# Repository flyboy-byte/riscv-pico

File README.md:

<h1 align="center">riscv-pico</h1>

<p align="center">
  <strong>A Raspberry Pi Pico running real Linux, with its own keyboard and screen.</strong><br>
  The RP2040 emulates a RISC-V CPU, SPI PSRAM becomes system memory,<br>
  and the Linux guest drives real GPIO pins.
</p>

<p align="center">
  <a href="https://flyboy-byte.github.io/riscv-pico/"><b>Website</b></a> •
  <a href="#try-it-in-60-seconds-no-hardware">Try it</a> •
  <a href="#how-it-actually-works">How it works</a> •
  <a href="#build-one-yourself">Build one</a> •
  <a href="#programming-on-the-pico">Programming</a> •
  <a href="#downloads">Downloads</a> •
  <a href="PLAN.md">PLAN.md</a>
</p>

<p align="center">
  <b>The story, photos, full pin map and wiring diagrams:
  <a href="https://flyboy-byte.github.io/riscv-pico/">flyboy-byte.github.io/riscv-pico</a></b>
</p>

---

> [!NOTE]
> **This is a build log, not an upstream improvement.** It's my own vibe-coded "Linux on a Pico"
> project — the real projects below did the hard work; this repo forks, ports, and glues them
> together and writes down what happened. Posted in case it's useful to someone chasing the same
> idea. The code, docs, and this README were written by
> [Claude Code](https://claude.com/claude-code); I directed it, tested on real hardware, and made
> the calls.

### Built on

| Project | What it gave this repo |
| --- | --- |
| **[tvlad1234/pico-rv32ima](https://github.com/tvlad1234/pico-rv32ima)** + **[tiny-rv32ima](https://github.com/tvlad1234/tiny-rv32ima)** | **The fork point.** Actively maintained, the emulator core, and the VGA and PS/2 console code. |
| [ElectroBoy404NotFound/pico-linux](https://github.com/ElectroBoy404NotFound/pico-linux) | The multi-chip PSRAM port and LCD console approach. |
| [cnlohr/mini-rv32ima](https://github.com/cnlohr/mini-rv32ima) | The original RV32IMA-in-C emulator all of the above descends from. |
| [xhackerustc/uc-rv32ima](https://github.com/xhackerustc/uc-rv32ima) | The cache implementation this actually runs. |
| [rswier/c4](https://github.com/rswier/c4) via [tvlad1234/c4](https://github.com/tvlad1234/c4) | The C compiler that runs on the machine itself. |

**Go star their repos, not this one.**

---

## The short version

A Pico has no MMU and about 264 KB of RAM. It was never meant to run an operating system. So:
core 1 of the RP2040 runs a full RV32IMA interpreter, two SPI PSRAM chips stand in for system
memory, and an SD card holds the kernel and root filesystem. Linux boots on top of that — and
custom kernel drivers let the guest reach back out through the emulator to drive **real hardware**.

Add a PS/2 keyboard, a VGA monitor and a breadboard power supply, and it runs with no computer
attached. You can write a program in nano on the Pico, run it, and have it blink an LED.

<p align="center"><sub>The OLED is reporting on the machine it's plugged into: 16 MB across 2 chips, live MIPS, uptime, 400 MHz clock.</sub></p>

And running on its own: PS/2 keyboard in, VGA monitor out, no PC anywhere.

| | |
|---|---|
|  |  |
| `sysinfo`: Linux 6.6 on an emulated RV32, 14 MB of RAM | GNU nano editing `hello.c`, full screen |
|  |  |
| Tiny BASIC, then c4 compiling and running that `hello.c` | Minesweeper, in Lua |

---

## Status

What's actually verified, versus what merely compiles. No wishful thinking in this table.

| | Feature | Notes |
|---|---|---|
| ✅ | **Linux boots on a real Pico** | RP2040, 16 MB PSRAM, 60 MB rootfs off SD. Shell in well under a minute. |
| ✅ | **Runs standalone** | PS/2 keyboard in, VGA out, its own power supply. Files edited and saved with no PC attached. |
| ✅ | **GPIO from Linux → real pins** | Both `/dev/gpiochipN` (chardev + `libgpiod`) *and* `/sys/class/gpio`. Verified lighting an actual LED. |
| ✅ | **Runs real software** | Tiny BASIC, Lua 5.4.7, GNU nano 7.2 (full-screen), `sysinfo`, and minesweeper. |
| ✅ | **nano on the VGA screen** | Firmware v6 rewrote the VGA terminal as a VT102, so nano draws correctly at 53×30. Verified on hardware. On v5, nano over VGA is unusable. |
| ✅ | **Custom kernel drivers** | Block device, GPIO, second console channel — real Linux drivers, not shims. |
| ✅ | **Desktop harness** | Boots the same kernel on your PC in a few seconds. No hardware needed. |
| ✅ | **SSD1306 OLED panel** | A live stats visualizer. Not essential, just fun. |
| ✅ | **Programming on the Pico** | Lua with sleep and raw key input, GPIO from Lua and the shell, the c4 C compiler, BASIC's `BYE`, and minesweeper. All verified on hardware. |
| ✅ | **Slimmer kernel** | Networking removed, about 1 MB of RAM back. Boots on hardware. |
| 🚧 | **`pico2` / `pico2_w` (RP2350)** | Builds clean for all four board targets. Never actually flashed. |
| ❌ | **Networking on the Pico** | Removed on purpose for the RAM. The stack and a half-built host bridge live on in [`net-v1`](https://github.com/flyboy-byte/riscv-pico/releases/tag/net-v1). |
| ❌ | **I²C / SPI / PWM / ADC for the guest** | Documented as an idea in [PLAN.md](PLAN.md). Deliberately not built. |

---

## Try it in 60 seconds (no hardware)

A desktop build of the **real** emulator core, booting the same SD card image the Pico uses.

```sh
git clone https://github.com/flyboy-byte/riscv-pico && cd riscv-pico
harness/build.sh

mkdir images
REL=https://github.com/flyboy-byte/riscv-pico/releases/download/sdcard-v2
curl -L $REL/riscv-pico-sdcard-v2.tar.gz | tar xz -C images

# lay the three files out on a FAT image, the way the firmware expects
dd if=/dev/zero of=harness/disk.img bs=1M count=80
mformat -F -i harness/disk.img ::
mcopy -i harness/disk.img images/IMAGE images/DTB images/ROOTFS ::

python3 harness/desktop_terminal.py harness/disk.img
```

Needs `mtools`, plus `PyQt6` and `python-pyte` (`sudo pacman -S python-pyte` on Arch). Boots to a
shell in a couple of seconds. Then try:

| Command | What happens |
| --- | --- |
| `lua /root/blink.lua 3` | Blinks GPIO line 0 three times. The harness prints each pin change |
| `c4 /root/hello.c` | Compiles and runs C on the emulated machine |
| `basic` | Tiny BASIC. `BYE` gets you back out |
| `lua /root/mines.lua` | Minesweeper. Arrow keys, space digs, `f` flags, `q` quits |
| `nano`, `sysinfo`, `gpioinfo gpiochip0` | Editor, system banner, the GPIO chip |

> [!IMPORTANT]
> **These images won't boot under stock `mini-rv32ima`.** This project's emulator core adds custom
> block-device and console CSRs that upstream doesn't implement, so `harness/build.sh` builds this
> repo's own desktop copy of the *real* core instead. Background in [CLAUDE.md](CLAUDE.md).

---

## How it actually works

The interesting part isn't that Linux boots. It's that the emulated guest can reach **real
hardware** — so `echo 1 > /sys/class/gpio/gpio512/value`, typed into a Linux shell, ends with
current flowing out of a physical pin.

```
┌─────────────────────────────────────────────────────────────────┐
│  RISC-V Linux guest                                 (emulated)  │
│                                                                 │
│      shell  ·  BASIC  ·  Lua  ·  c4  ·  nano                    │
│                       │                                         │
│      Linux 6.6, nommu, RV32IMA                                  │
│                       │                                         │
│      drivers:  gpio-tinyrv32  ·  block  ·  console              │
└───────────────────────┬─────────────────────────────────────────┘
                        │   CSR instructions   (GPIO = 0x1a0-0x1a3)
┌───────────────────────┴─────────────────────────────────────────┐
│  RP2040  @ 400 MHz                              (real silicon)  │
│                                                                 │
│      core 1  ──▶  tiny-rv32ima, the RV32IMA interpreter         │
│      core 0  ──▶  CSR handlers, VGA, PS/2, OLED                 │
└───────────────────────┬─────────────────────────────────────────┘
                        │
     ┌──────────────────┼──────────────────┬──────────────────┐
     ▼                  ▼                  ▼                  ▼
 2x SPI PSRAM      microSD card        GPIO pins        console I/O
 16 MB = RAM     kernel + rootfs     LEDs, buttons    PS/2, VGA, OLED
```

Linux sees ordinary devices — a block device, a `gpiochip`, a console. The RP2040 does the
translating underneath. Full GPIO walkthrough, including wiring an LED and the exact ioctls, is in
**[docs/GPIO_AND_BASIC_TUTORIAL.md](docs/GPIO_AND_BASIC_TUTORIAL.md)**. The
**[website](https://flyboy-byte.github.io/riscv-pico/)** draws the whole machine, including where
the 16 MB of memory actually lives.

---

## Build one yourself

The whole path, start to finish. No compiler needed: the firmware and the SD card image are both
prebuilt.

| Step | Do this | Where |
| --- | --- | --- |
| 1 | Buy the parts | [Parts](#parts--about-20-for-the-core) |
| 2 | Wire it: PSRAM and SD card first, keyboard and VGA after | [Wiring](#wiring) |
| 3 | Flash the firmware: hold BOOTSEL, plug in, copy one `.uf2` file | [Firmware](#firmware) |
| 4 | Put three files on a FAT32 microSD card | [SD card](#sd-card) |
| 5 | Power on, **press any key**, wait for the `~ #` prompt | [First boot](#first-boot) |
| 6 | Blink an LED, edit a file, play minesweeper | [Programming on the Pico](#programming-on-the-pico) |

### Parts — about $20 for the core

Everything here is what's on the verified build. No minimum order quantities, all single-quantity
friendly. Prices drift; this isn't a live feed.

| Part | Qty | Notes |
| --- | --- | --- |
| Raspberry Pi Pico | 1 | Verified on a Pico H (RP2040). Builds for `pico_w`/`pico2`/`pico2_w` too, but RP2350 is untested. |
| **APS6404L-3SQR-SN** PSRAM, SOP-8 | 2 | 8 MB each → 16 MB. [ProtoSupplies](https://protosupplies.com/product/psram/), ~$2.39 ea. |
| [SMD→DIP 8-pin adapter](https://protosupplies.com/product/pcb-smd-soic-8-msop-8-tssop-8-to-dip-adapter5-pack/) | 1 pack | ~$0.79 for 5. Headers not included. The PSRAM is surface-mount; these get it onto 0.1" pitch. |
| microSD breakout, SPI | 1 | Any 3.3 V module labelled `3V3 CS MOSI CLK MISO GND`. |
| microSD card | 1 | **4–32 GB, FAT32.** Not SDXC/exFAT — Petit FatFs only speaks FAT12/16/32. |
| 10 kΩ resistor | 1 | Pull-up for `SIO2`/`SIO3` on both chips. One resistor covers all four pins. |
| SSD1306 OLED, 128×64 | 0–1 | Optional. Must be the **I²C** 4-pin variant, not SPI. |
| Decoupling caps | a few | 100 nF ceramic + 10–100 µF bulk. Cheap insurance — see the power warning below. |
| Breadboard + jumpers | — | |
| Micro-USB cable | 1 | Flashing the firmware, and the serial console. |

To run it without a PC, add:

| Part | Qty | Notes |
| --- | --- | --- |
| **[Serial Wombat PCB_0024 VGA breakout](https://www.amazon.com/Breakout-Resistors-Serial-Wombat-Arduino/dp/B0D4F7H59M)** | 1 | Resistors already fitted. Plug in an ordinary VGA cable; six jumpers to the Pico. |
| VGA monitor + cable | 1 | Anything that takes 640×480 at 60 Hz. |
| PS/2 keyboard | 1 | A real PS/2 keyboard, not a USB keyboard on a passive purple adapter. |
| PS/2 socket breakout | 0–1 | Or do what this build did: cut the keyboard's cable and solder its four wires to a scrap of perfboard with jumper wires. |
| Logic level converter, BSS138 4-channel | 1 | PS/2 is a 5 V bus. Only the keyboard needs it. |
| USB-C breadboard power supply | 1 | 5 V rail powers the Pico and keyboard; 3.3 V rail powers the SD card and OLED. |

> [!CAUTION]
> **Get the `-SN` (SOP-8) suffix, not `-ZR`.** Same silicon, but `-ZR` is USON-8 — a 3×2 mm
> leadless package that is genuinely painful to hand-solder or rework. Plain `APS6404L-3SQR` with
> no suffix is bare die, not a packaged part at all.

**Substitutes work fine.** ESP-PSRAM64H, LY68L6400, and IPUS equivalents share the SOP-8 pinout and
the `0x5D` known-good-die ID the firmware checks for. For stock across distributors, try
[Findchips](https://www.findchips.com/search/APS6404L-3SQR-SN) or
[Octopart](https://octopart.com/search?q=APS6404L-3SQR-SN).

### Wiring

The core build is 3.3 V native and its console is USB serial, so no adapter is needed. The
**[website](https://flyboy-byte.github.io/riscv-pico/)** has the full 40-pin map, a power and
ground diagram, and a [VGA wiring bench card](https://flyboy-byte.github.io/riscv-pico/vga.html).

> [!WARNING]
> **On the SD card module, `MOSI` and `CLK` cross over.** The module's header order does not match
> the Pico's pin order. This is the single easiest mistake to make on the whole board, and it costs
> you an afternoon.

> [!WARNING]
> **The PS/2 keyboard runs at 5 V, and RP2040 pins are not 5 V tolerant.** Route `CLK` and `DATA`
> through the level converter. Before the Pico is connected, meter the converter's low-voltage
> outputs: they must idle at 3.3 V, never 5 V. A resistor divider does not work on this bus.

<details>
<summary><b>PSRAM — two chips on a shared SPI bus</b></summary>

<br>

They differ only in chip-select:

| Chip pin | Signal | Chip 1 | Chip 2 |
| --- | --- | --- | --- |
| 1 | `/CE` | GP13 (pin 17) | GP14 (pin 19) |
| 2 | `SO` | GP12 (pin 16) | GP12 — shared |
| 5 | `SI` | GP11 (pin 15) | GP11 — shared |
| 6 | `SCLK` | GP10 (pin 14) | GP10 — shared |
| 3, 7 | `SIO2`, `SIO3` | → 3V3 via one shared 10 kΩ | same |
| 4, 8 | `VSS`, `VDD` | GND, 3V3 | GND, 3V3 |

`SIO2`/`SIO3` go unused in SPI mode. Pull them **high**, not low — some pin-compatible parts put an
active-low `/RESET` or `/HOLD` on `SIO3`. One 10 kΩ covers all four pins; nothing ever drives them.

**Default build is two-chip / 16 MB** (`PSRAM_TWO_CHIPS 1` in `hw_config.h`, `EMULATOR_RAM_MB 16` in
`vm_config.h`). Going single-chip? Set them to `0` and `8`. Mismatching them is a compile-time
`#error`, not a silent address-wrap bug that bites you three hours later.
`PSRAM_SPI_SPEED_MHZ` defaults to 20, which stays stable even on messy breadboard leads.

</details>

<details>
<summary><b>microSD card module</b></summary>

<br>

| Module | Pico |
| --- | --- |
| `CS` | GP0 (pin 1) |
| `MOSI` | GP3 (pin 5) |
| `CLK` | GP2 (pin 4) |
| `MISO` | GP4 (pin 6) |

⚠️ **`MOSI` and `CLK` cross over** — see the warning above. The module's header order does not
match the Pico's pin order.

The card itself is plain FAT32 with `IMAGE`, `DTB`, and `ROOTFS` in the root. No special
formatting.

</details>

<details>
<summary><b>PS/2 keyboard, through the level converter</b></summary>

<br>

| Keyboard (mini-DIN-6) | Converter | Pico |
| --- | --- | --- |
| Pin 1, `DATA` | HV1 → LV1 | GP26 (pin 31) |
| Pin 5, `CLK` | HV2 → LV2 | GP27 (pin 32) |
| Pin 4, +5 V | HV | 5 V rail of the breadboard supply |
| Pin 3, GND | GND | Common ground |
| — | LV | 3V3 OUT (pin 36) |

Wire colours are not standardised, so identify pins with a meter rather than by colour. Getting
`DATA` and `CLK` swapped is harmless; if no keys arrive, swap them. The driver only receives, so
Caps Lock and Num Lock lights never come on. No firmware change is needed — the keyboard driver is
already in the firmware.

</details>

<details>
<summary><b>VGA, through the Serial Wombat PCB_0024 breakout</b></summary>

<br>

Use the breakout's **outer** header column, which is its 3.3 V input. The inner column is sized for
5 V and gives a dim picture.

| Breakout | Pico |
| --- | --- |
| `V` | GP16 (pin 21) |
| `H` | GP17 (pin 22) |
| `GND` header | GND (pin 23) |
| `R` | GP18 (pin 24) |
| `G` | GP19 (pin 25) |
| `B` | GP20 (pin 26) |

Reading the column bottom to top lands on the Pico's pins in order, so the jumpers run straight.
Leave the five round pads along the top and the solder jumpers on the back unconnected. Green and
blue aren't configurable in firmware: they always follow red on the next two pins. The picture is
320×240 in eight colours, and the terminal is 53×30 characters.

</details>

<details>
<summary><b>SSD1306 OLED status panel (optional)</b></summary>

<br>

Four separate jumpers — there's no free adjacent GPIO pair left on the board:

| Module | Pico |
| --- | --- |
| `VCC` | 3.3 V from a **separate supply**, not pin 36 — see the power warning below |
| `GND` | GND (pin 28), tied to that supply's ground at one point |
| `SDA` | GP28 (pin 34) |
| `SCL` | GP21 (pin 27) |

Shows RAM/PSRAM config, boot stage, live MIPS, uptime, and clock — a stats panel, not a second
console. It runs on core 0, which the emulator never touches, and probes at boot: with nothing
attached, the firmware behaves exactly as if the code weren't there. Disable entirely with
`CONSOLE_OLED 0` in `hw_config.h`. If a panel is wired but stays blank, try `OLED_I2C_ADDR 0x3D`.
It runs alongside VGA without conflict.

</details>

<details>
<summary><b>Running without a PC</b></summary>

<br>

Feed the breadboard supply's **5 V** rail into **VSYS (pin 39)**. Never feed 3.3 V into pin 36: that
is the output of the Pico's own regulator, not an input. With USB unplugged there's no serial
console, so the VGA screen shows the boot. Before pulling power, run `sync` or `halt`, or the ext2
root filesystem can be damaged.

</details>

> [!WARNING]
> **Breadboard power is the thing that will actually bite you.** Wiring up the OLED destabilised
> the PSRAM bus and crashed boot — despite the two sharing no GPIO pins at all. The cause was a
> single 3V3 supply pin feeding PSRAM VCC, both chips' pull-ups, the SD card *and* the OLED, so any
> load spike on that node bled into everything else on it.
>
> The fix was a single-point (star) power layout: separate supply for OLED/SD, PSRAM on its own
> clean VCC/GND, short jumpers, and decoupling caps at each chip's supply pins. **If you see random
> resets or PSRAM failures that only appear once a second peripheral is wired up, check power
> distribution before you suspect the chip.** Full writeup — including the wrong theories tried
> first — in [PLAN.md](PLAN.md) and [docs/HARDWARE_SCHEMATIC.md](docs/HARDWARE_SCHEMATIC.md).

### Firmware

**Just want to flash something?** Grab
**[`pico-rv32ima-boards-v6`](https://github.com/flyboy-byte/riscv-pico/releases/tag/pico-rv32ima-boards-v6)**
— prebuilt `.uf2` for all four board variants, ready to go. It includes the VGA, PS/2 and OLED
consoles, and a VGA terminal that full-screen programs like nano can draw on.

<details>
<summary><b>Or build it from source</b></summary>

<br>

```sh
# once — Pico SDK, shallow clone with just the tinyusb submodule (~65 MB)
git clone -b 2.1.1 --depth 1 https://github.com/raspberrypi/pico-sdk.git ~/pico-sdk
git -C ~/pico-sdk submodule update --init --depth 1 lib/tinyusb

firmware/build.sh              # all four boards → firmware/out/*.uf2
firmware/build.sh pico2_w      # or just one
```

About 150 KB per board. Flash by holding **BOOTSEL** while plugging in the Pico — it mounts as a
USB drive called `RPI-RP2` — then copy the `.uf2` across.

</details>

### SD card

1. Format a 4–32 GB microSD card as **FAT32**.
2. From **[`sdcard-v2`](https://github.com/flyboy-byte/riscv-pico/releases/tag/sdcard-v2)**, download `IMAGE`, `DTB` and `ROOTFS`. The same three
   files are also bundled as `riscv-pico-sdcard-v2.tar.gz`.
3. Copy all three to the root of the card, not into a folder. Their names must stay exactly as they
   are.

### First boot

Plug the Pico into a PC over USB and open its serial console: `screen /dev/ttyACM0 115200` on
Linux, or PuTTY on the new COM port on Windows. With the VGA screen attached you can skip this and
watch the monitor instead.

1. The console prints `PSRAM OK`, then `SD init OK`, and **waits for a keypress**. Press any key,
   on the serial console or on the PS/2 keyboard. On the VGA screen, all you see before that is
   the `pico-rv32ima, compiled …` banner.
2. `Loading kernel image`, then `Starting RISC-V VM`, then the Linux boot log.
3. A `~ #` shell prompt, in well under a minute. Try `sysinfo`.

Before unplugging, type `halt`, or at least `sync`. The root filesystem is ext2 and doesn't
survive a hard power-off well.

<details>
<summary><b>If it doesn't boot</b></summary>

<br>

| You see | Likely cause |
| --- | --- |
| Nothing at all over USB serial | Firmware not flashed, or the console opened too late. Press a key; the boot waits for one anyway. |
| `PANIC: PSRAM ERR`, repeating | PSRAM wiring or power. Check `/CE` on GP13/GP14, the 10 kΩ pull-up, and that each chip has 3.3 V and ground. |
| `PANIC: Error initalizing SD` | `MOSI`/`CLK` swapped (the most common mistake), the card isn't FAT32, or the module isn't 3.3 V. |
| `PANIC: Error opening image file` | The card is readable but `IMAGE` isn't in its root, or it was renamed. |
| Boots, then random resets once the OLED or SD is added | Power distribution. See the warning above. |
| VGA monitor says "no signal" | Check V and H on GP16/GP17 and the ground jumper. The monitor must accept 640×480 at 60 Hz. |
| Keyboard does nothing | Swap `DATA` and `CLK`. Check the converter's low side idles at 3.3 V. |
| `System hasn't been cleanly shutdown` | Harmless warning after a power-off without `halt`. |

</details>

---

## Programming on the Pico

You can write and run programs on the machine itself: open a file in nano, save it, run it. No PC.

| Language | Try | Notes |
| --- | --- | --- |
| **Lua 5.4** | `lua blink.lua` | Adds `sys.sleep(seconds)`, `sys.ms()` and `sys.raw()`, which stock Lua lacks. GPIO goes through `/sys/class/gpio`. |
| **C, via c4** | `c4 gpio_set.c 1` | Compiles C to bytecode and interprets it. This copy adds `for` and `write`, and it can compile itself. |
| **Tiny BASIC** | `basic` | Line-numbered BASIC. `BYE` returns to the shell. |
| **Shell** | `sh script.sh` | busybox `hush`, not bash. |

Every command for all of this is on one page in
**[docs/CHEATSHEET.md](docs/CHEATSHEET.md)**. A shorter copy sized for the VGA screen is on the card:
`nano -v /root/help.txt` pages through it when there's no PC attached.

The examples are in `/root` on the SD image. Blinking an LED in Lua looks like this:

```lua
local function put(path, text)
  local f = io.open(path, "w"); f:write(text); f:close()
end

put("/sys/class/gpio/export", "512")                 -- GPIO line 0 = Pico GP1, pin 2
put("/sys/class/gpio/gpio512/direction", "out")
for i = 1, 10 do
  put("/sys/class/gpio/gpio512/value", "1"); sys.sleep(0.2)
  put("/sys/class/gpio/gpio512/value", "0"); sys.sleep(0.2)
end
put("/sys/class/gpio/unexport", "512")               -- release it, or gpioset says busy
```

There's a game, too: **`lua /root/mines.lua`** is minesweeper on the VGA screen. Arrow keys move,
space digs, `f` flags, `r` restarts, `q` quits. Board size is optional —
`lua /root/mines.lua 20 14 40`. Single keypresses need `sys.raw()`, another call the Lua build adds;
where that isn't available it falls back to typed commands, so it works over a pipe too.

`os.execute` and `io.popen` don't work from Lua here: they need `fork()`, which a no-MMU machine
doesn't have. Details on c4's language and limits are in
**[apps/c4/README.md](apps/c4/README.md)**.

<details>
<summary><b>Cross-compiling bigger programs on a PC</b></summary>

<br>

There's a real cross-compiler for this target — `riscv32-buildroot-linux-uclibc-gcc`, producing the
`bFLT` no-MMU binary format the kernel needs. `apps/` holds the hand-written pieces: Tiny BASIC
(`basic.c`), the Lua `sys` extension (`lua_sys.c`), c4, a GPIO chardev smoke test (`gpiotest.c`),
and `sysinfo.sh`. Lua 5.4.7 and GNU nano 7.2 build straight from unmodified upstream sources and
aren't vendored here.

The toolchain isn't checked in; grab
[`toolchain-v2`](https://github.com/flyboy-byte/riscv-pico/releases/tag/toolchain-v2). The rebuild
recipe and the gotchas already solved live in PLAN.md's "Cross-compile toolchain", "Real GNU nano"
and "apps/" sections.

</details>

---

## Downloads

Build outputs ship as GitHub releases rather than committed binaries, which keeps `git clone` fast.

| Release | Contents |
| --- | --- |
| **[`sdcard-v2`](https://github.com/flyboy-byte/riscv-pico/releases/tag/sdcard-v2)** | **Current SD card image.** No-network kernel; rootfs with Lua, c4, BASIC and examples, with the console sized for the VGA screen. Hardware-verified. |
| **[`pico-rv32ima-boards-v6`](https://github.com/flyboy-byte/riscv-pico/releases/tag/pico-rv32ima-boards-v6)** | **Current firmware**, all four boards — 16 MB two-chip, VGA with a rewritten VT102 terminal, PS/2 with working Home/End/Delete/Page keys, OLED panel, GPIO CSRs. |
| [`toolchain-v2`](https://github.com/flyboy-byte/riscv-pico/releases/tag/toolchain-v2) | The cross-compiler, wchar-enabled (needed for nano/ncurses). |
| [`rv32harness-v1`](https://github.com/flyboy-byte/riscv-pico/releases/tag/rv32harness-v1) | Desktop harness binaries, x86-64 Linux. |
| [`kernel-gpio-v2`](https://github.com/flyboy-byte/riscv-pico/releases/tag/kernel-gpio-v2) | Previous kernel + rootfs, with networking. Hardware-verified. |
| [`net-v1`](https://github.com/flyboy-byte/riscv-pico/releases/tag/net-v1) | The networking reference: TCP/IP stack and the second console channel's SLIP work. |
| [`apps-v1`](https://github.com/flyboy-byte/riscv-pico/releases/tag/apps-v1), [`apps-v2`](https://github.com/flyboy-byte/riscv-pico/releases/tag/apps-v2) | Older loose binaries. Everything current is in `sdcard-v2`. |

Firmware `-v5` boots `sdcard-v2`, but nano on its VGA screen is unusable. `-v3`/`-v4` still boot
too. `-v1`/`-v2` are superseded single-chip 8 MB builds that don't boot the current rootfs.

---

## Repo layout

| Path | What | Notes |
| --- | --- | --- |
| `harness/` | *this repo* | Desktop build of the real emulator core, plus a PyQt6 terminal app to drive it. |
| `firmware/` | *this repo* | `build.sh` — one command, `.uf2`s for all four board targets. |
| `apps/` | *this repo* | Programs for the target: Tiny BASIC, the Lua `sys` extension, examples. |
| `apps/c4/` | [rswier](https://github.com/rswier/c4) via [tvlad1234](https://github.com/tvlad1234/c4) | The on-device C compiler, with `for` and `write` added here. GPL-2.0. |
| `buildroot-overlay/` | *this repo* | Kernel config and the patches that create every custom device — block, GPIO, second console. |
| `site/` | *this repo* | The [website](https://flyboy-byte.github.io/riscv-pico/). Plain HTML, published to `gh-pages`. |
| `docs/` | *this repo* | GPIO and BASIC tutorial, hardware schematic handoff notes, images. |
| `experiments/` | *this repo* | Side quests, like a Raspberry Pi 4 pretending to be an SD card. |
| `upstream/pico-rv32ima/` | [tvlad1234](https://github.com/tvlad1234/pico-rv32ima) | The fork this builds on. No longer pristine — the PSRAM port lives here. |
| `upstream/pico-rv32ima/tiny-rv32ima/` | [tvlad1234](https://github.com/tvlad1234/tiny-rv32ima) | The emulator core. Also edited by the same port. |
| `upstream/pico-linux/` | [ElectroBoy404NotFound](https://github.com/ElectroBoy404NotFound/pico-linux) | Reference only, still pristine. Source of the PSRAM port logic. |

All three `upstream/` paths are `git subtree`s with full history, so `git log -- upstream/<x>` works
and upstream changes can still be pulled — commands in [CLAUDE.md](CLAUDE.md).

**[PLAN.md](PLAN.md) is the living state doc** — every decision, every bug, every dead end, and
what's next. It's far more detailed than this file.

---

## License

This repo's own code (`harness/`, `apps/`, `firmware/`, `buildroot-overlay/`, `site/`, docs) is MIT —
see [LICENSE](LICENSE) — **except `apps/c4/`, which is GPL-2.0** like the c4 it comes from. Everything
under `upstream/` keeps its original licensing (MIT / Apache-2.0 / BSD-3); see the `LICENSE` in each
subtree.

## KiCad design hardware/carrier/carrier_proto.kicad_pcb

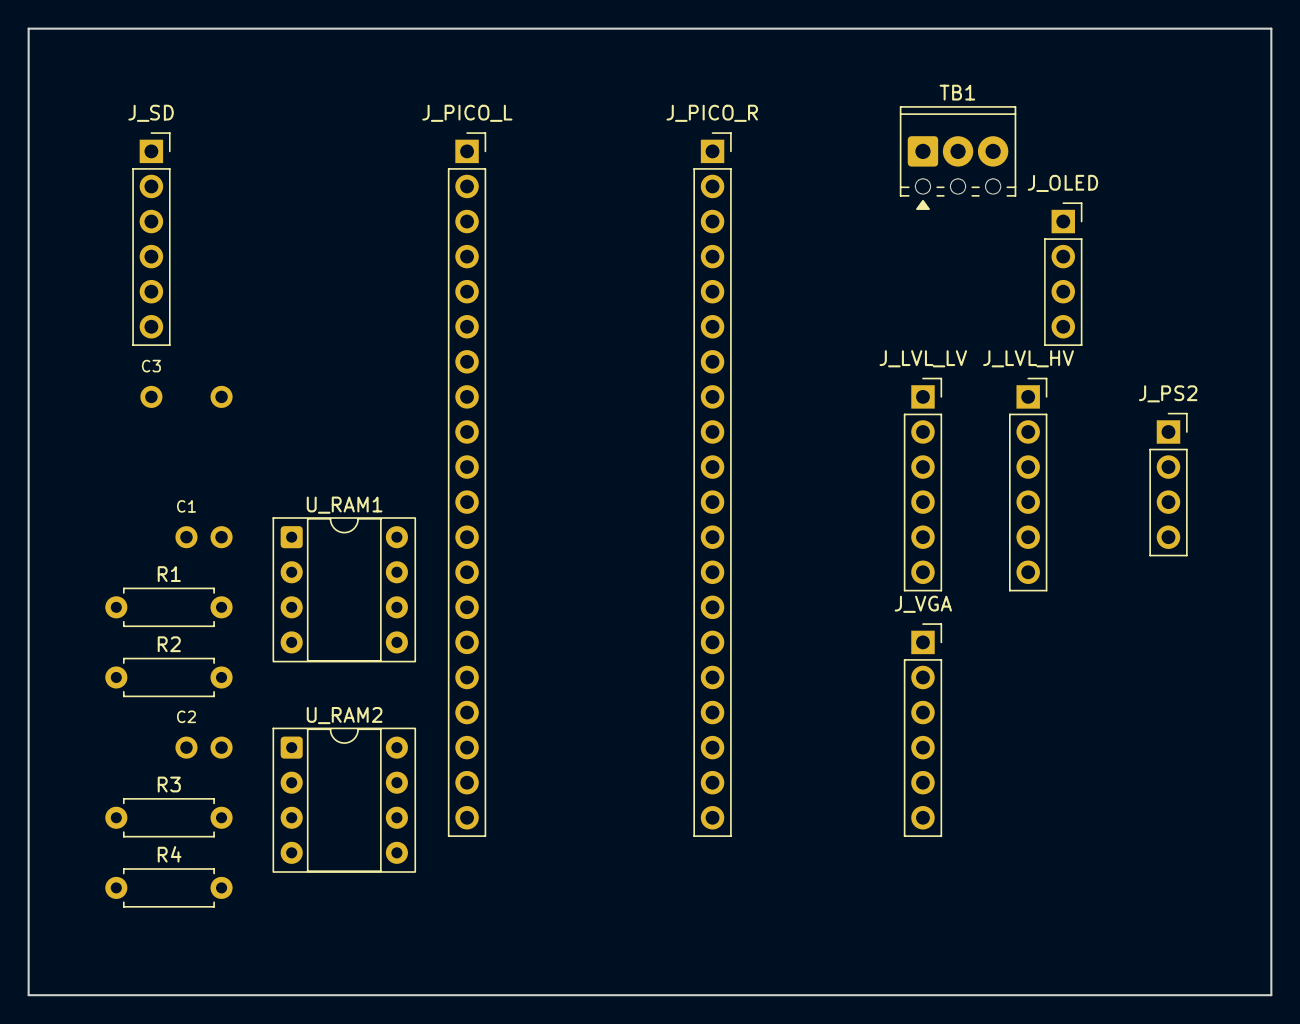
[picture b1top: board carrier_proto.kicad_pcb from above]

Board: 2 copper layers, 90.0 x 70.0 mm, 18 parts (0 on the bottom side), 28 nets, no tracks yet.

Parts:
C1: 100n RAM1; C_THT_P2.54mm
C2: 100n RAM2; C_THT_P2.54mm
C3: 10u bulk; C_THT_P5.08mm
J_LVL_HV: BSS138 4ch level converter -; PinSocket_1x06_P2.54mm_Vertical
J_LVL_LV: BSS138 4ch level converter -; PinSocket_1x06_P2.54mm_Vertical
J_OLED: SSD1306 128x64 0.96in; PinSocket_1x04_P2.54mm_Vertical
J_PICO_L: Pico L; PinSocket_1x20_P2.54mm_Vertical
J_PICO_R: Pico R; PinSocket_1x20_P2.54mm_Vertical
J_PS2: PS/2 socket breakout; PinSocket_1x04_P2.54mm_Vertical
J_SD: microSD SPI breakout; PinSocket_1x06_P2.54mm_Vertical
J_VGA: Serial Wombat PCB_0024 VGA b; PinSocket_1x06_P2.54mm_Vertical
R1, R2, R3, R4: 10k; R_Axial_DIN0207_L6.3mm_D2.5mm_P7.62mm_Horizontal
TB1: 3-way screw terminal 2.54mm; TerminalBlock_Phoenix_MPT-0,5-3-2.54_1x03_P2.54mm_Horizontal
U_RAM1, U_RAM2: PSRAM APS6404L on DIP-8 adap; DIP-8_W7.62mm_Socket

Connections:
+3V3_EXT: C3.1, J_LVL_LV.1, J_OLED.2, J_SD.5, TB1.2
+3V3_PICO: C1.1, C2.1, J_PICO_R.5, R1.2, R2.2, R3.2, R4.2, U_RAM1.8, U_RAM2.8
+5V_EXT: J_LVL_HV.1, J_PICO_R.2, J_PS2.3, TB1.1
GND: C1.2, C2.2, C3.2, J_LVL_HV.6, J_LVL_LV.6, J_OLED.1, J_PICO_L.3, J_PICO_L.8, J_PICO_L.13, J_PICO_L.18, J_PICO_R.3, J_PICO_R.8, J_PICO_R.13, J_PICO_R.18, J_PS2.4, J_SD.6, J_VGA.6, TB1.3, U_RAM1.4, U_RAM2.4
OLED_SCL: J_OLED.3, J_PICO_R.14
OLED_SDA: J_OLED.4, J_PICO_R.7
PS2_CK_HV: J_LVL_HV.3, J_PS2.2
PS2_CK_LV: J_LVL_LV.3, J_PICO_R.9
PS2_DATA_HV: J_LVL_HV.2, J_PS2.1
PS2_DATA_LV: J_LVL_LV.2, J_PICO_R.10
PSRAM_CS1: J_PICO_L.17, U_RAM1.1
PSRAM_CS2: J_PICO_L.19, U_RAM2.1
PSRAM_MISO: J_PICO_L.16, U_RAM1.2, U_RAM2.2
PSRAM_MOSI: J_PICO_L.15, U_RAM1.5, U_RAM2.5
PSRAM_SCK: J_PICO_L.14, U_RAM1.6, U_RAM2.6
RAM1_HOLD: R2.1, U_RAM1.7
RAM1_WP: R1.1, U_RAM1.3
RAM2_HOLD: R4.1, U_RAM2.7
RAM2_WP: R3.1, U_RAM2.3
SD_CS: J_PICO_L.1, J_SD.1
SD_MISO: J_PICO_L.6, J_SD.4
SD_MOSI: J_PICO_L.5, J_SD.3
SD_SCK: J_PICO_L.4, J_SD.2
VGA_B: J_PICO_R.15, J_VGA.5
VGA_G: J_PICO_R.16, J_VGA.4
VGA_HSYNC: J_PICO_R.19, J_VGA.2
VGA_R: J_PICO_R.17, J_VGA.3
VGA_VSYNC: J_PICO_R.20, J_VGA.1

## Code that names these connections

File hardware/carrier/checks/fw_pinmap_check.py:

#!/usr/bin/env python3
"""pinmap.csv must agree with the firmware's hw_config.h.

Every pin on this board is compiled into firmware. If someone edits hw_config.h and the board is
already built, the board is wrong and nothing else in this project will notice -- the layout, the
build sheet and the wire list would all still be self-consistent. So this check reads the firmware
header directly and compares it against pinmap.csv's fw_pin column.

One result line, exit 0/1.
"""

import csv
import os
import re
import sys

HERE = os.path.dirname(os.path.abspath(__file__))
PROJ = os.path.dirname(HERE)
HW_CONFIG = os.path.normpath(os.path.join(
    PROJ, "..", "..", "upstream", "pico-rv32ima", "pico-rv32ima", "hw_config.h"))

# firmware #define -> the signal name pinmap.csv uses
EXPECT = {
    "SD_SPI_PIN_CS": "SD_CS",
    "SD_SPI_PIN_CK": "SD_SCK",
    "SD_SPI_PIN_TX": "SD_MOSI",
    "SD_SPI_PIN_RX": "SD_MISO",
    "PSRAM_SPI_PIN_CK": "PSRAM_SCK",
    "PSRAM_SPI_PIN_TX": "PSRAM_MOSI",
    "PSRAM_SPI_PIN_RX": "PSRAM_MISO",
    "PSRAM_SPI_PIN_S1": "PSRAM_CS1",
    "PSRAM_SPI_PIN_S2": "PSRAM_CS2",
    "VGA_VSYNC_PIN": "VGA_VSYNC",
    "VGA_HSYNC_PIN": "VGA_HSYNC",
    "VGA_R_PIN": "VGA_R",
    "PS2_PIN_DATA": "PS2_DATA",
    "PS2_PIN_CK": "PS2_CK",
    "OLED_I2C_PIN_SDA": "OLED_SDA",
    "OLED_I2C_PIN_SCL": "OLED_SCL",
}
# VGA green and blue are not #defined: the PIO program takes them as VGA_R_PIN + 1 and + 2.
DERIVED = {"VGA_G": ("VGA_R_PIN", 1), "VGA_B": ("VGA_R_PIN", 2)}


def main():
    if not os.path.exists(HW_CONFIG):
        print("SKIPPED firmware pinmap: %s not found" % HW_CONFIG)
        return 0

    text = open(HW_CONFIG).read()
    fw = {}
    for name in list(EXPECT) + ["VGA_R_PIN"]:
        m = re.search(r"^#define\s+%s\s+(\d+)" % re.escape(name), text, re.M)
        if m:
            fw[name] = int(m.group(1))

    want = {}
    for define, signal in EXPECT.items():
        if define in fw:
            want[signal] = fw[define]
    for signal, (base, offset) in DERIVED.items():
        if base in fw:
            want[signal] = fw[base] + offset

    have = {}
    with open(os.path.join(PROJ, "pinmap.csv")) as fh:
        for row in csv.DictReader(l for l in fh if not l.startswith("#")):
            sig, fwpin = row.get("signal"), (row.get("fw_pin") or "").strip()
            if sig and fwpin.startswith("GP"):
                have[sig] = int(fwpin[2:])

    problems = []
    for signal, gpio in sorted(want.items()):
        if signal not in have:
            problems.append("%s is GP%d in hw_config.h but missing from pinmap.csv" % (signal, gpio))
        elif have[signal] != gpio:
            problems.append("%s is GP%d in hw_config.h but GP%d in pinmap.csv"
                            % (signal, gpio, have[signal]))
    for signal, gpio in sorted(have.items()):
        if signal not in want and signal in EXPECT.values():
            problems.append("%s is in pinmap.csv but no longer #defined in hw_config.h" % signal)

    if problems:
        print("FAIL firmware pinmap: %d disagreement(s) with hw_config.h" % len(problems))
        for p in problems:
            print("  " + p)
        return 1
    print("PASS firmware pinmap: %d signals match hw_config.h" % len(want))
    return 0


if __name__ == "__main__":
    sys.exit(main())
